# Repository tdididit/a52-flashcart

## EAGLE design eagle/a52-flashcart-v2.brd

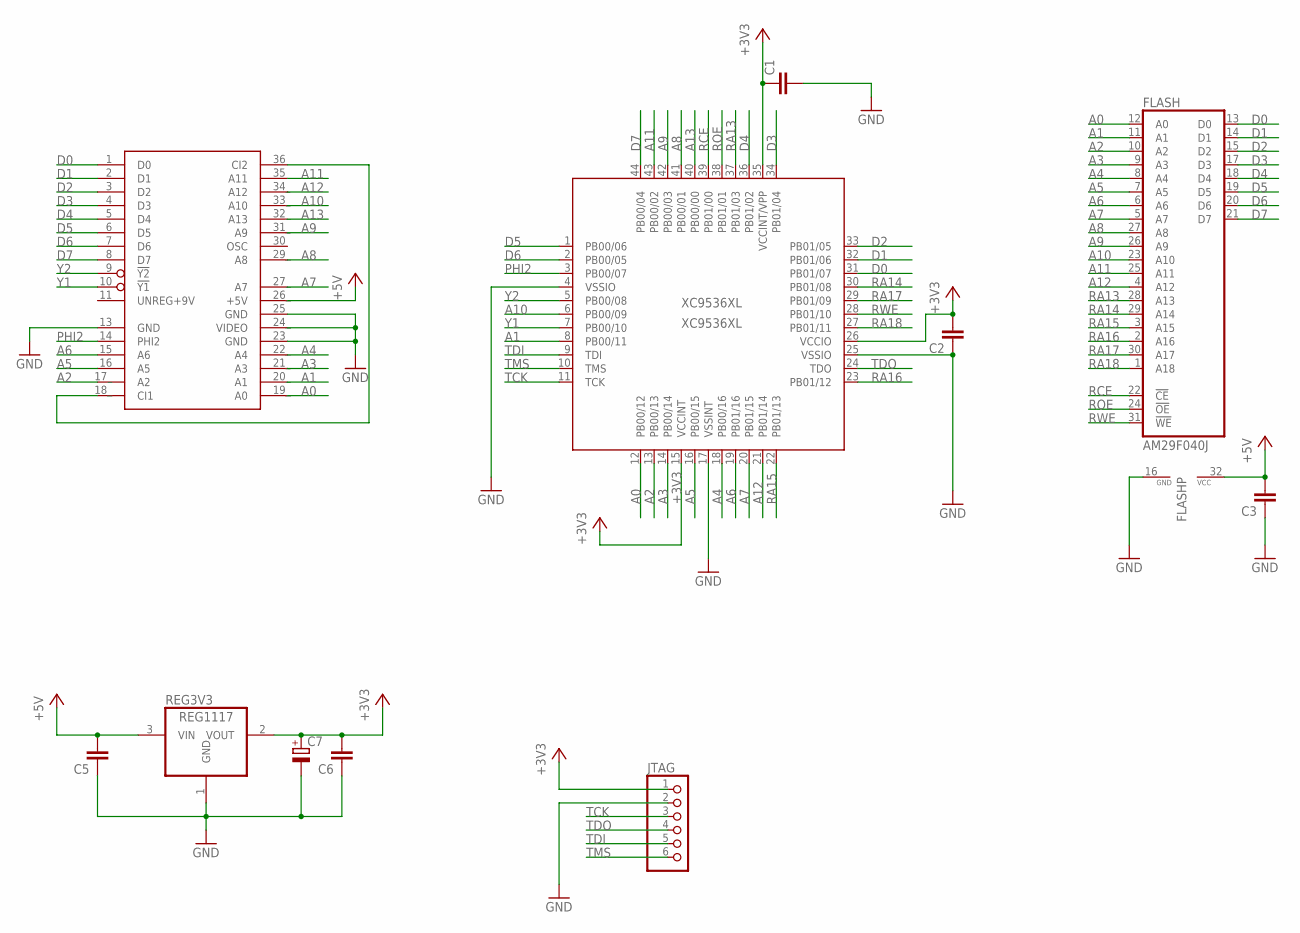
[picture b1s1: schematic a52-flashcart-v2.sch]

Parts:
C1, C2, C3, C5, C6: C-EUC0603; C0603
C7: CPOL-EUSMCC; SMC_C
FLASH: AM29F040J; PLCC32R
JTAG: PINHD-1X6; 1X06
REG3V3: REG1117; SOT223
U$1: ATARI-5200-TS; ATARI-5200-SMALL-T
XC9536XL: XC9536XL; SQFP-S-10X10-44

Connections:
+3V3: C1.1, C2.2, C6.2, C7.+, JTAG.1, REG3V3.2 (VOUT), XC9536XL.15 (VCCINT), XC9536XL.26 (VCCIO), XC9536XL.35 (VCCINT/VPP)
+5V: C3.2, C5.2, FLASH.32 (VCC), REG3V3.3 (VIN), U$1.26_ (+5V)
A0: FLASH.12 (A0), U$1.19_ (A0), XC9536XL.12 (PB00/12)
A1: FLASH.11 (A1), U$1.20_ (A1), XC9536XL.8 (PB00/11)
A2: FLASH.10 (A2), U$1.17_ (A2), XC9536XL.13 (PB00/13)
A3: FLASH.9 (A3), U$1.21_ (A3), XC9536XL.14 (PB00/14)
A4: FLASH.8 (A4), U$1.22_ (A4), XC9536XL.18 (PB00/16)
A5: FLASH.7 (A5), U$1.16 (A5), XC9536XL.16 (PB00/15)
A6: FLASH.6 (A6), U$1.15 (A6), XC9536XL.19 (PB01/16)
A7: FLASH.5 (A7), U$1.27_ (A7), XC9536XL.20 (PB01/15)
A8: FLASH.27 (A8), U$1.29_ (A8), XC9536XL.41 (PB00/01)
A9: FLASH.26 (A9), U$1.31_ (A9), XC9536XL.42 (PB00/03)
A10: FLASH.23 (A10), U$1.33_ (A10), XC9536XL.6 (PB00/09)
A11: FLASH.25 (A11), U$1.35 (A11), XC9536XL.43 (PB00/02)
A12: FLASH.4 (A12), U$1.34_ (A12), XC9536XL.21 (PB01/14)
A13: U$1.32_ (A13), XC9536XL.40 (PB00/00)
D0: FLASH.13 (D0), U$1.1 (D0), XC9536XL.31 (PB01/07)
D1: FLASH.14 (D1), U$1.2 (D1), XC9536XL.32 (PB01/06)
D2: FLASH.15 (D2), U$1.3 (D2), XC9536XL.33 (PB01/05)
D3: FLASH.17 (D3), U$1.4 (D3), XC9536XL.34 (PB01/04)
D4: FLASH.18 (D4), U$1.5 (D4), XC9536XL.36 (PB01/02)
D5: FLASH.19 (D5), U$1.6 (D5), XC9536XL.1 (PB00/06)
D6: FLASH.20 (D6), U$1.7 (D6), XC9536XL.2 (PB00/05)
D7: FLASH.21 (D7), U$1.8 (D7), XC9536XL.44 (PB00/04)
GND: C1.2, C2.1, C3.1, C5.1, C6.1, C7.-, FLASH.16 (GND), JTAG.2, REG3V3.1 (GND), U$1.13 (GND), U$1.23 (GND), U$1.24_ (VIDEO), U$1.25 (GND), XC9536XL.4 (VSSIO), XC9536XL.17 (VSSINT), XC9536XL.25 (VSSIO)
unnamed: U$1.18_ (CI1), U$1.36 (CI2)
PHI2: U$1.14 (PHI2), XC9536XL.3 (PB00/07)
RA13: FLASH.28 (A13), XC9536XL.37 (PB01/03)
RA14: FLASH.29 (A14), XC9536XL.30 (PB01/08)
RA15: FLASH.3 (A15), XC9536XL.22 (PB01/13)
RA16: FLASH.2 (A16), XC9536XL.23 (PB01/12)
RA17: FLASH.30 (A17), XC9536XL.29 (PB01/09)
RA18: FLASH.1 (A18), XC9536XL.27 (PB01/11)
RCE: FLASH.22 (!CE), XC9536XL.39 (PB01/00)
ROE: FLASH.24 (!OE), XC9536XL.38 (PB01/01)
RWE: FLASH.31 (!WE), XC9536XL.28 (PB01/10)
TCK: JTAG.3, XC9536XL.11 (TCK)
TDI: JTAG.5, XC9536XL.9 (TDI)
TDO: JTAG.4, XC9536XL.24 (TDO)
TMS: JTAG.6, XC9536XL.10 (TMS)
Y1: U$1.10 (!Y1), XC9536XL.7 (PB00/10)
Y2: U$1.9 (!Y2), XC9536XL.5 (PB00/08)

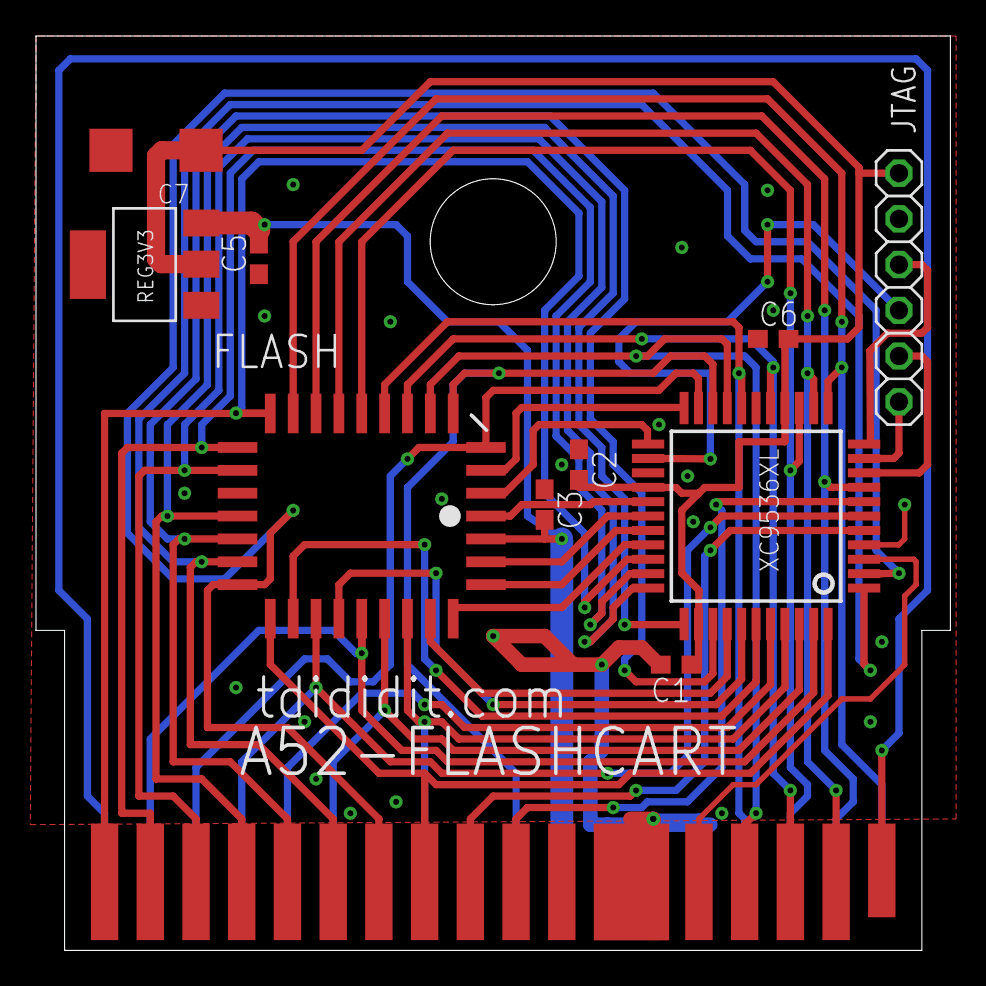
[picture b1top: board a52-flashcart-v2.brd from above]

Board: 2 copper layers, 50.8 x 50.8 mm, 11 parts (0 on the bottom side), 42 nets.

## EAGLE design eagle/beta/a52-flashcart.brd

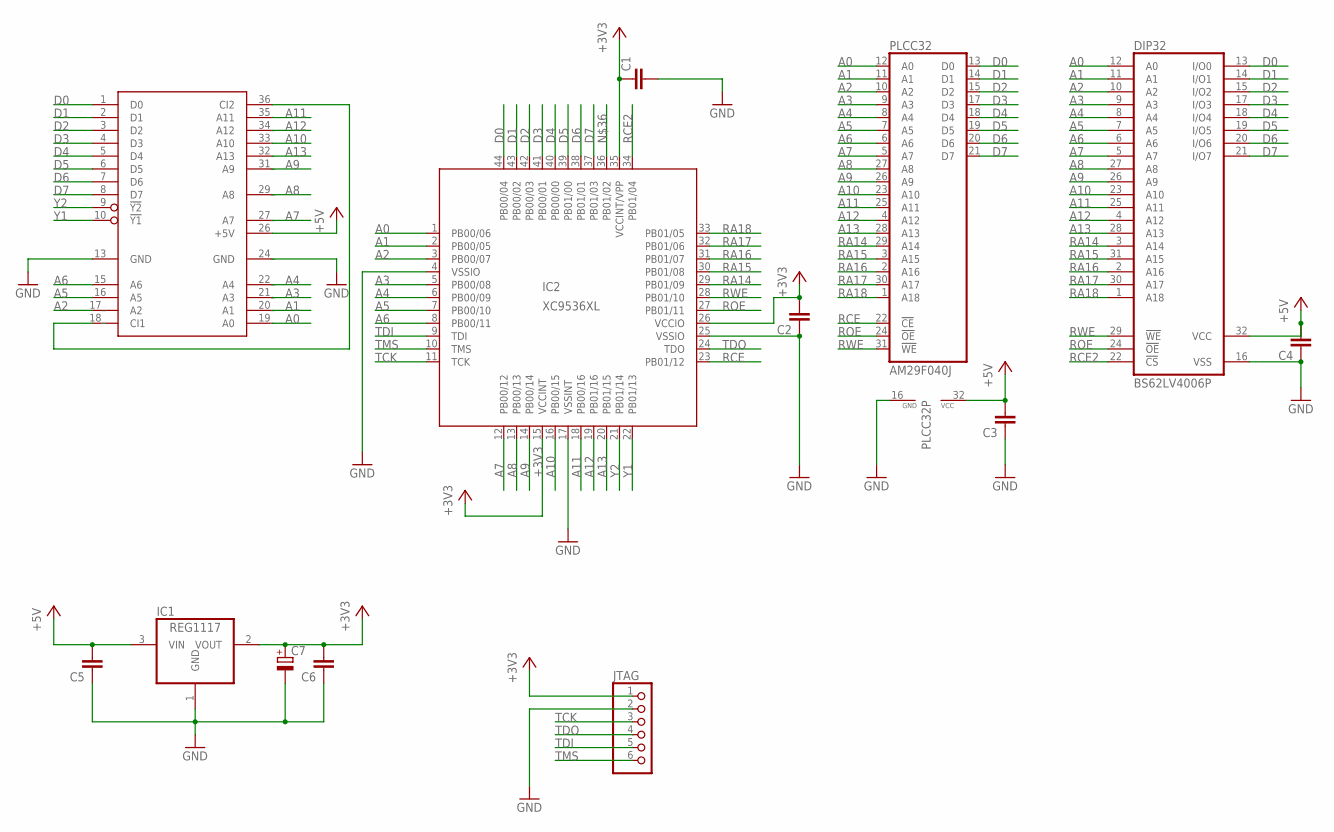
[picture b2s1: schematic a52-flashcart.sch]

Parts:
C1, C2, C3, C4, C5, C6: C-EUC0603; C0603
C7: CPOL-EUE2,5-6E; E25-6E
DIP32: BS62LV4006P; DIL-32
IC1: REG1117; SOT223
IC2: XC9536XL; SQFP-S-10X10-44
JTAG: PINHD-1X6; 1X06
PLCC32: AM29F040J; PLCC32R
U$1: ATARI-5200

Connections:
+3V3: C1.1, C2.2, C6.2, C7.+, IC1.2 (VOUT), IC2.15 (VCCINT), IC2.26 (VCCIO), IC2.35 (VCCINT/VPP), JTAG.1
+5V: C3.2, C4.2, C5.2, DIP32.32 (VCC), IC1.3 (VIN), PLCC32.32 (VCC), U$1.26_ (+5V)
A0: DIP32.12 (A0), IC2.1 (PB00/06), PLCC32.12 (A0), U$1.19_ (A0)
A1: DIP32.11 (A1), IC2.2 (PB00/05), PLCC32.11 (A1), U$1.20_ (A1)
A2: DIP32.10 (A2), IC2.3 (PB00/07), PLCC32.10 (A2), U$1.17_ (A2)
A3: DIP32.9 (A3), IC2.5 (PB00/08), PLCC32.9 (A3), U$1.21_ (A3)
A4: DIP32.8 (A4), IC2.6 (PB00/09), PLCC32.8 (A4), U$1.22_ (A4)
A5: DIP32.7 (A5), IC2.7 (PB00/10), PLCC32.7 (A5), U$1.16 (A5)
A6: DIP32.6 (A6), IC2.8 (PB00/11), PLCC32.6 (A6), U$1.15 (A6)
A7: DIP32.5 (A7), IC2.12 (PB00/12), PLCC32.5 (A7), U$1.27_ (A7)
A8: DIP32.27 (A8), IC2.13 (PB00/13), PLCC32.27 (A8), U$1.29_ (A8)
A9: DIP32.26 (A9), IC2.14 (PB00/14), PLCC32.26 (A9), U$1.31_ (A9)
A10: DIP32.23 (A10), IC2.16 (PB00/15), PLCC32.23 (A10), U$1.33_ (A10)
A11: DIP32.25 (A11), IC2.18 (PB00/16), PLCC32.25 (A11), U$1.35 (A11)
A12: DIP32.4 (A12), IC2.19 (PB01/16), PLCC32.4 (A12), U$1.34_ (A12)
A13: DIP32.28 (A13), IC2.20 (PB01/15), PLCC32.28 (A13), U$1.32_ (A13)
D0: DIP32.13 (I/O0), IC2.44 (PB00/04), PLCC32.13 (D0), U$1.1 (D0)
D1: DIP32.14 (I/O1), IC2.43 (PB00/02), PLCC32.14 (D1), U$1.2 (D1)
D2: DIP32.15 (I/O2), IC2.42 (PB00/03), PLCC32.15 (D2), U$1.3 (D2)
D3: DIP32.17 (I/O3), IC2.41 (PB00/01), PLCC32.17 (D3), U$1.4 (D3)
D4: DIP32.18 (I/O4), IC2.40 (PB00/00), PLCC32.18 (D4), U$1.5 (D4)
D5: DIP32.19 (I/O5), IC2.39 (PB01/00), PLCC32.19 (D5), U$1.6 (D5)
D6: DIP32.20 (I/O6), IC2.38 (PB01/01), PLCC32.20 (D6), U$1.7 (D6)
D7: DIP32.21 (I/O7), IC2.37 (PB01/03), PLCC32.21 (D7), U$1.8 (D7)
GND: C1.2, C2.1, C3.1, C4.1, C5.1, C6.1, C7.-, DIP32.16 (VSS), IC1.1 (GND), IC2.4 (VSSIO), IC2.17 (VSSINT), IC2.25 (VSSIO), JTAG.2, PLCC32.16 (GND), U$1.13 (GND), U$1.24_ (GND)
unnamed: U$1.18_ (CI1), U$1.36 (CI2)
RA14: DIP32.3 (A14), IC2.29 (PB01/09), PLCC32.29 (A14)
RA15: DIP32.31 (A15), IC2.30 (PB01/08), PLCC32.3 (A15)
RA16: DIP32.2 (A16), IC2.31 (PB01/07), PLCC32.2 (A16)
RA17: DIP32.30 (A17), IC2.32 (PB01/06), PLCC32.30 (A17)
RA18: DIP32.1 (A18), IC2.33 (PB01/05), PLCC32.1 (A18)
RCE: IC2.23 (PB01/12), PLCC32.22 (!CE)
RCE2: DIP32.22 (!CS), IC2.34 (PB01/04)
ROE: DIP32.24 (!OE), IC2.27 (PB01/11), PLCC32.24 (!OE)
RWE: DIP32.29 (!WE), IC2.28 (PB01/10), PLCC32.31 (!WE)
TCK: IC2.11 (TCK), JTAG.3
TDI: IC2.9 (TDI), JTAG.5
TDO: IC2.24 (TDO), JTAG.4
TMS: IC2.10 (TMS), JTAG.6
Y1: IC2.22 (PB01/13), U$1.10 (!Y1)
Y2: IC2.21 (PB01/14), U$1.9 (!Y2)

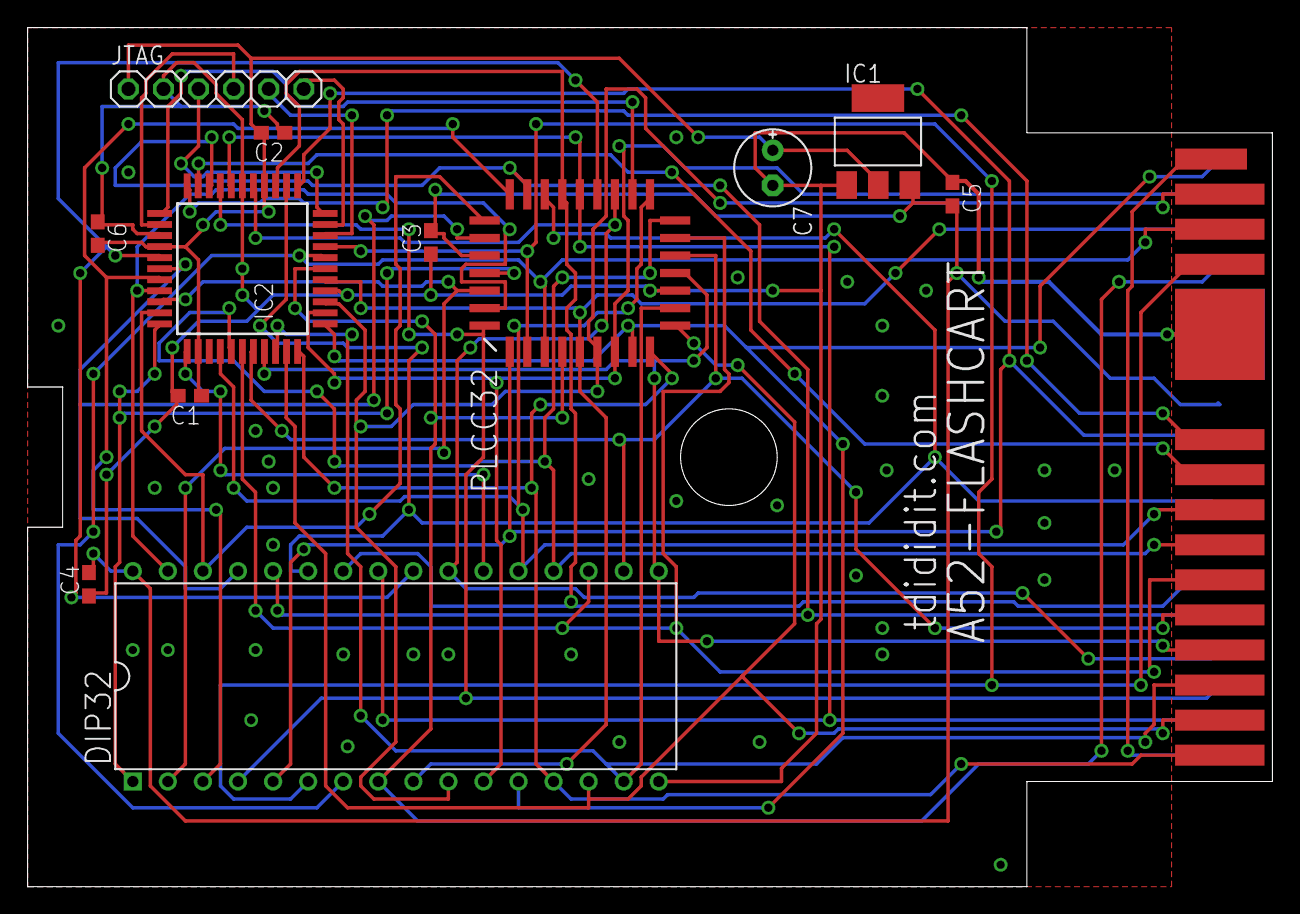
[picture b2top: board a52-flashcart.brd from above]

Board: 2 copper layers, 90.2 x 62.2 mm, 13 parts (0 on the bottom side), 41 nets.

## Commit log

2016-03-03 :octocat: Added .gitattributes
2016-03-19 update to v2
    added beta & final eagle production files + sketchup model
2016-03-23 board update - PHI2 signal connected to CPLD
